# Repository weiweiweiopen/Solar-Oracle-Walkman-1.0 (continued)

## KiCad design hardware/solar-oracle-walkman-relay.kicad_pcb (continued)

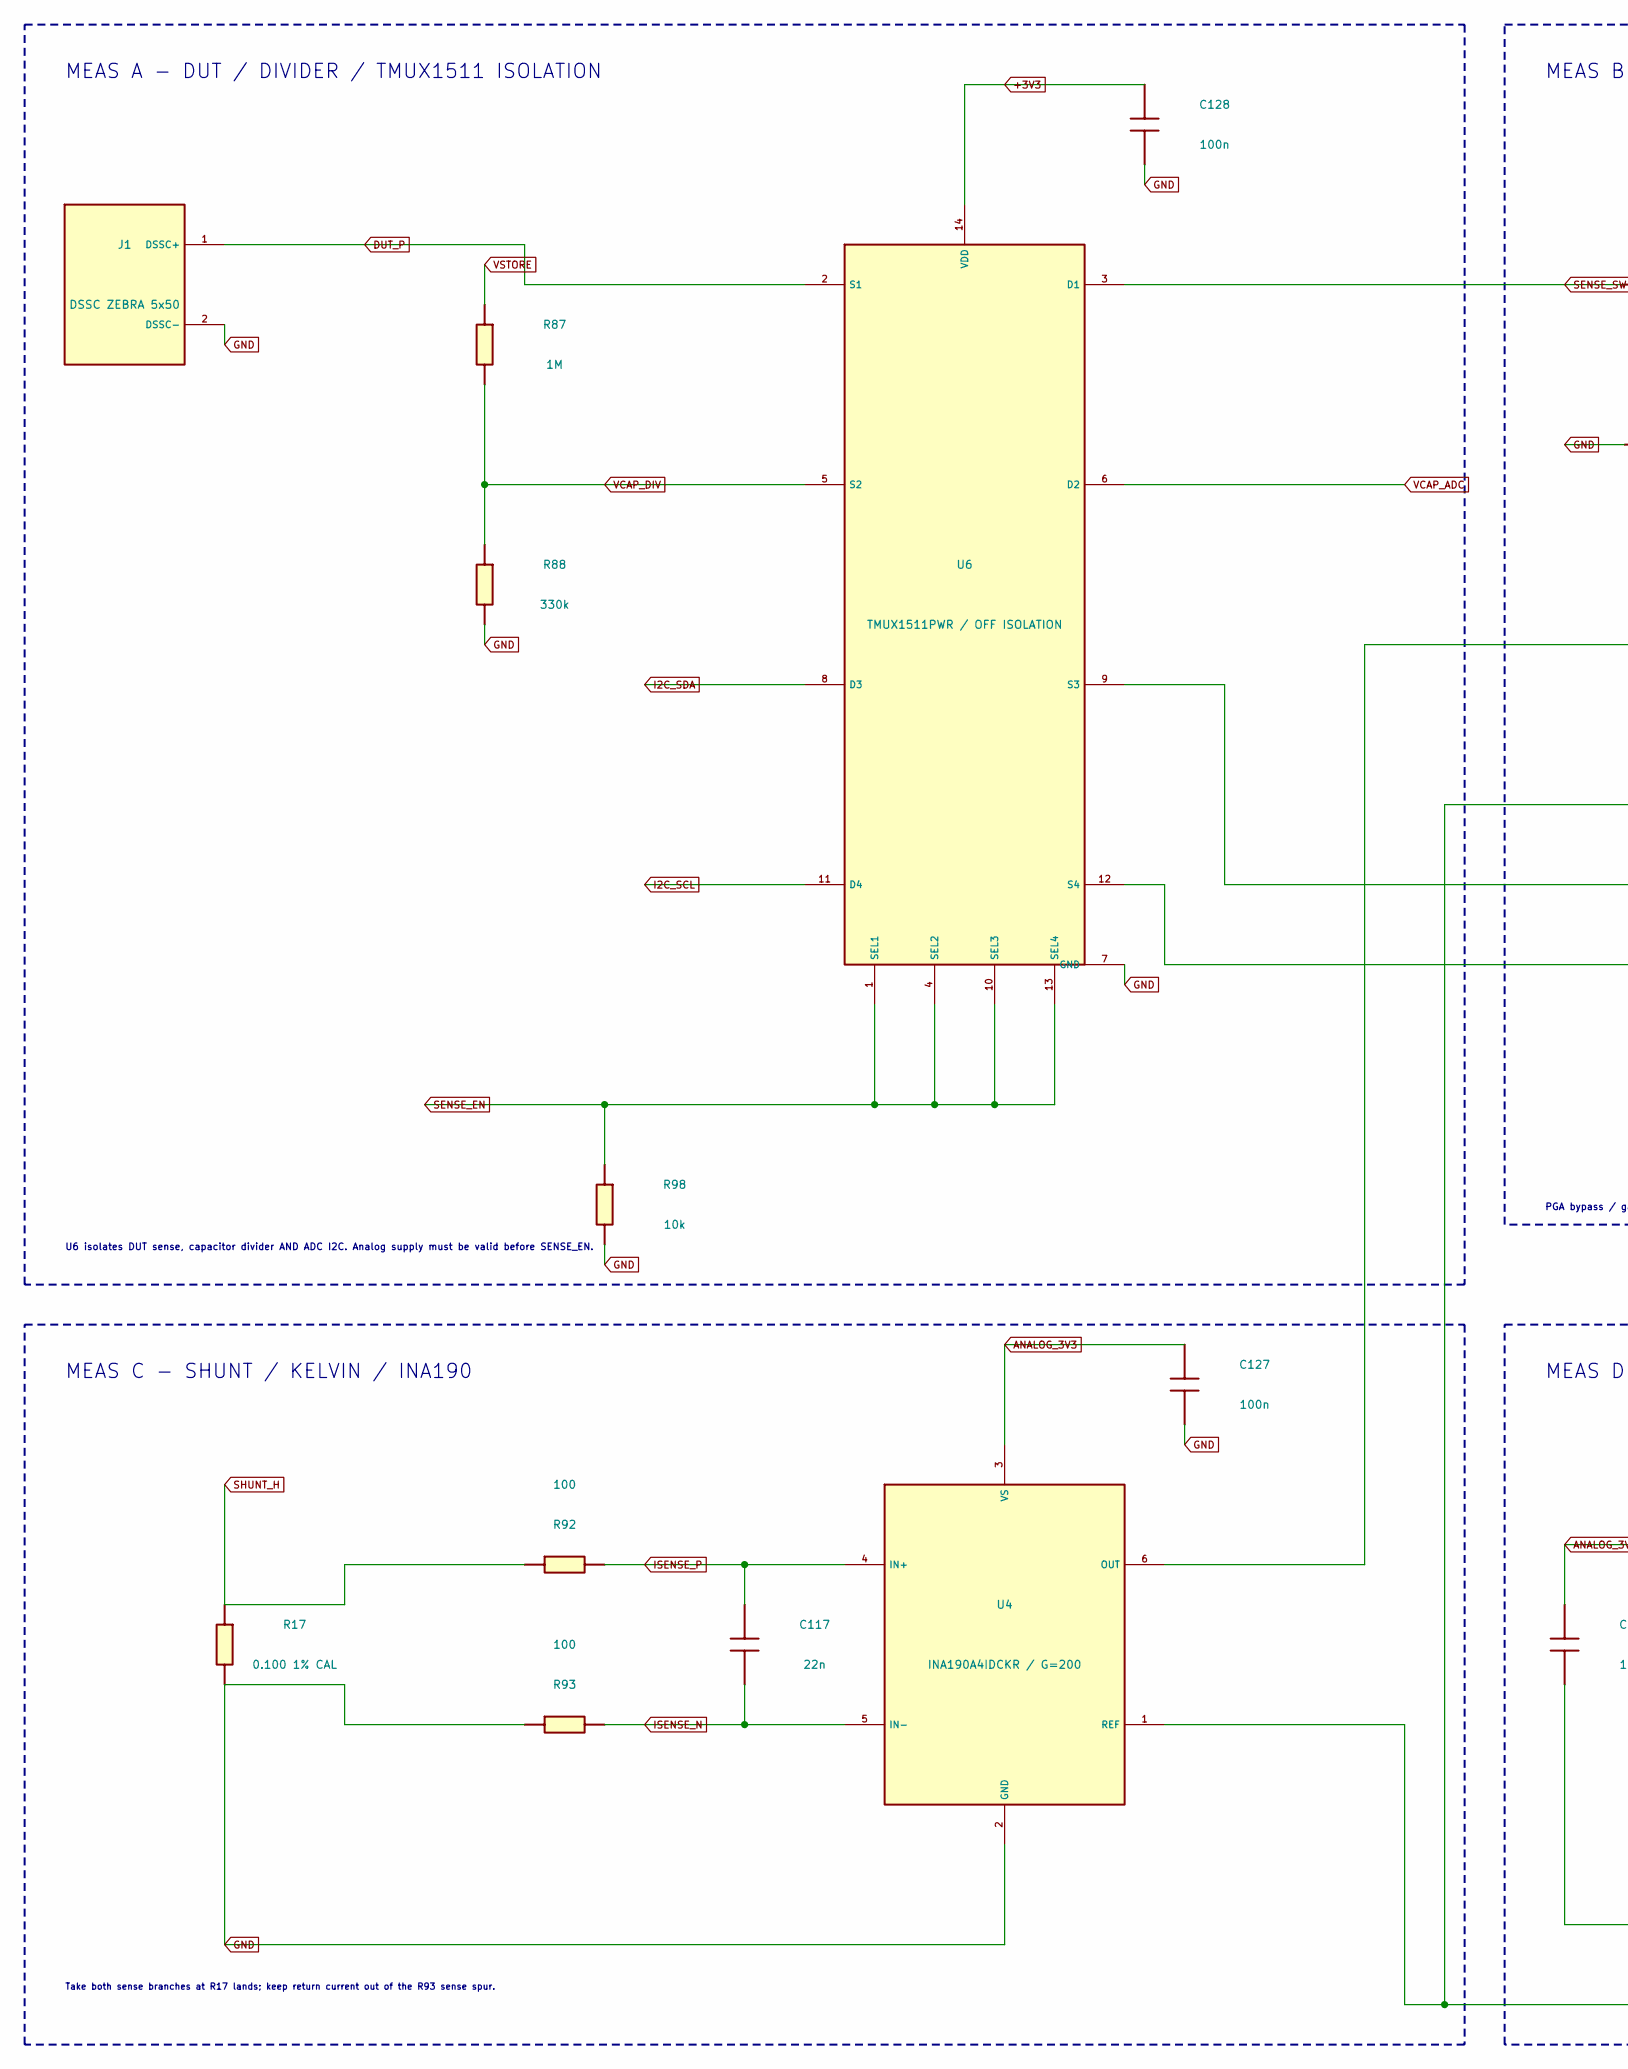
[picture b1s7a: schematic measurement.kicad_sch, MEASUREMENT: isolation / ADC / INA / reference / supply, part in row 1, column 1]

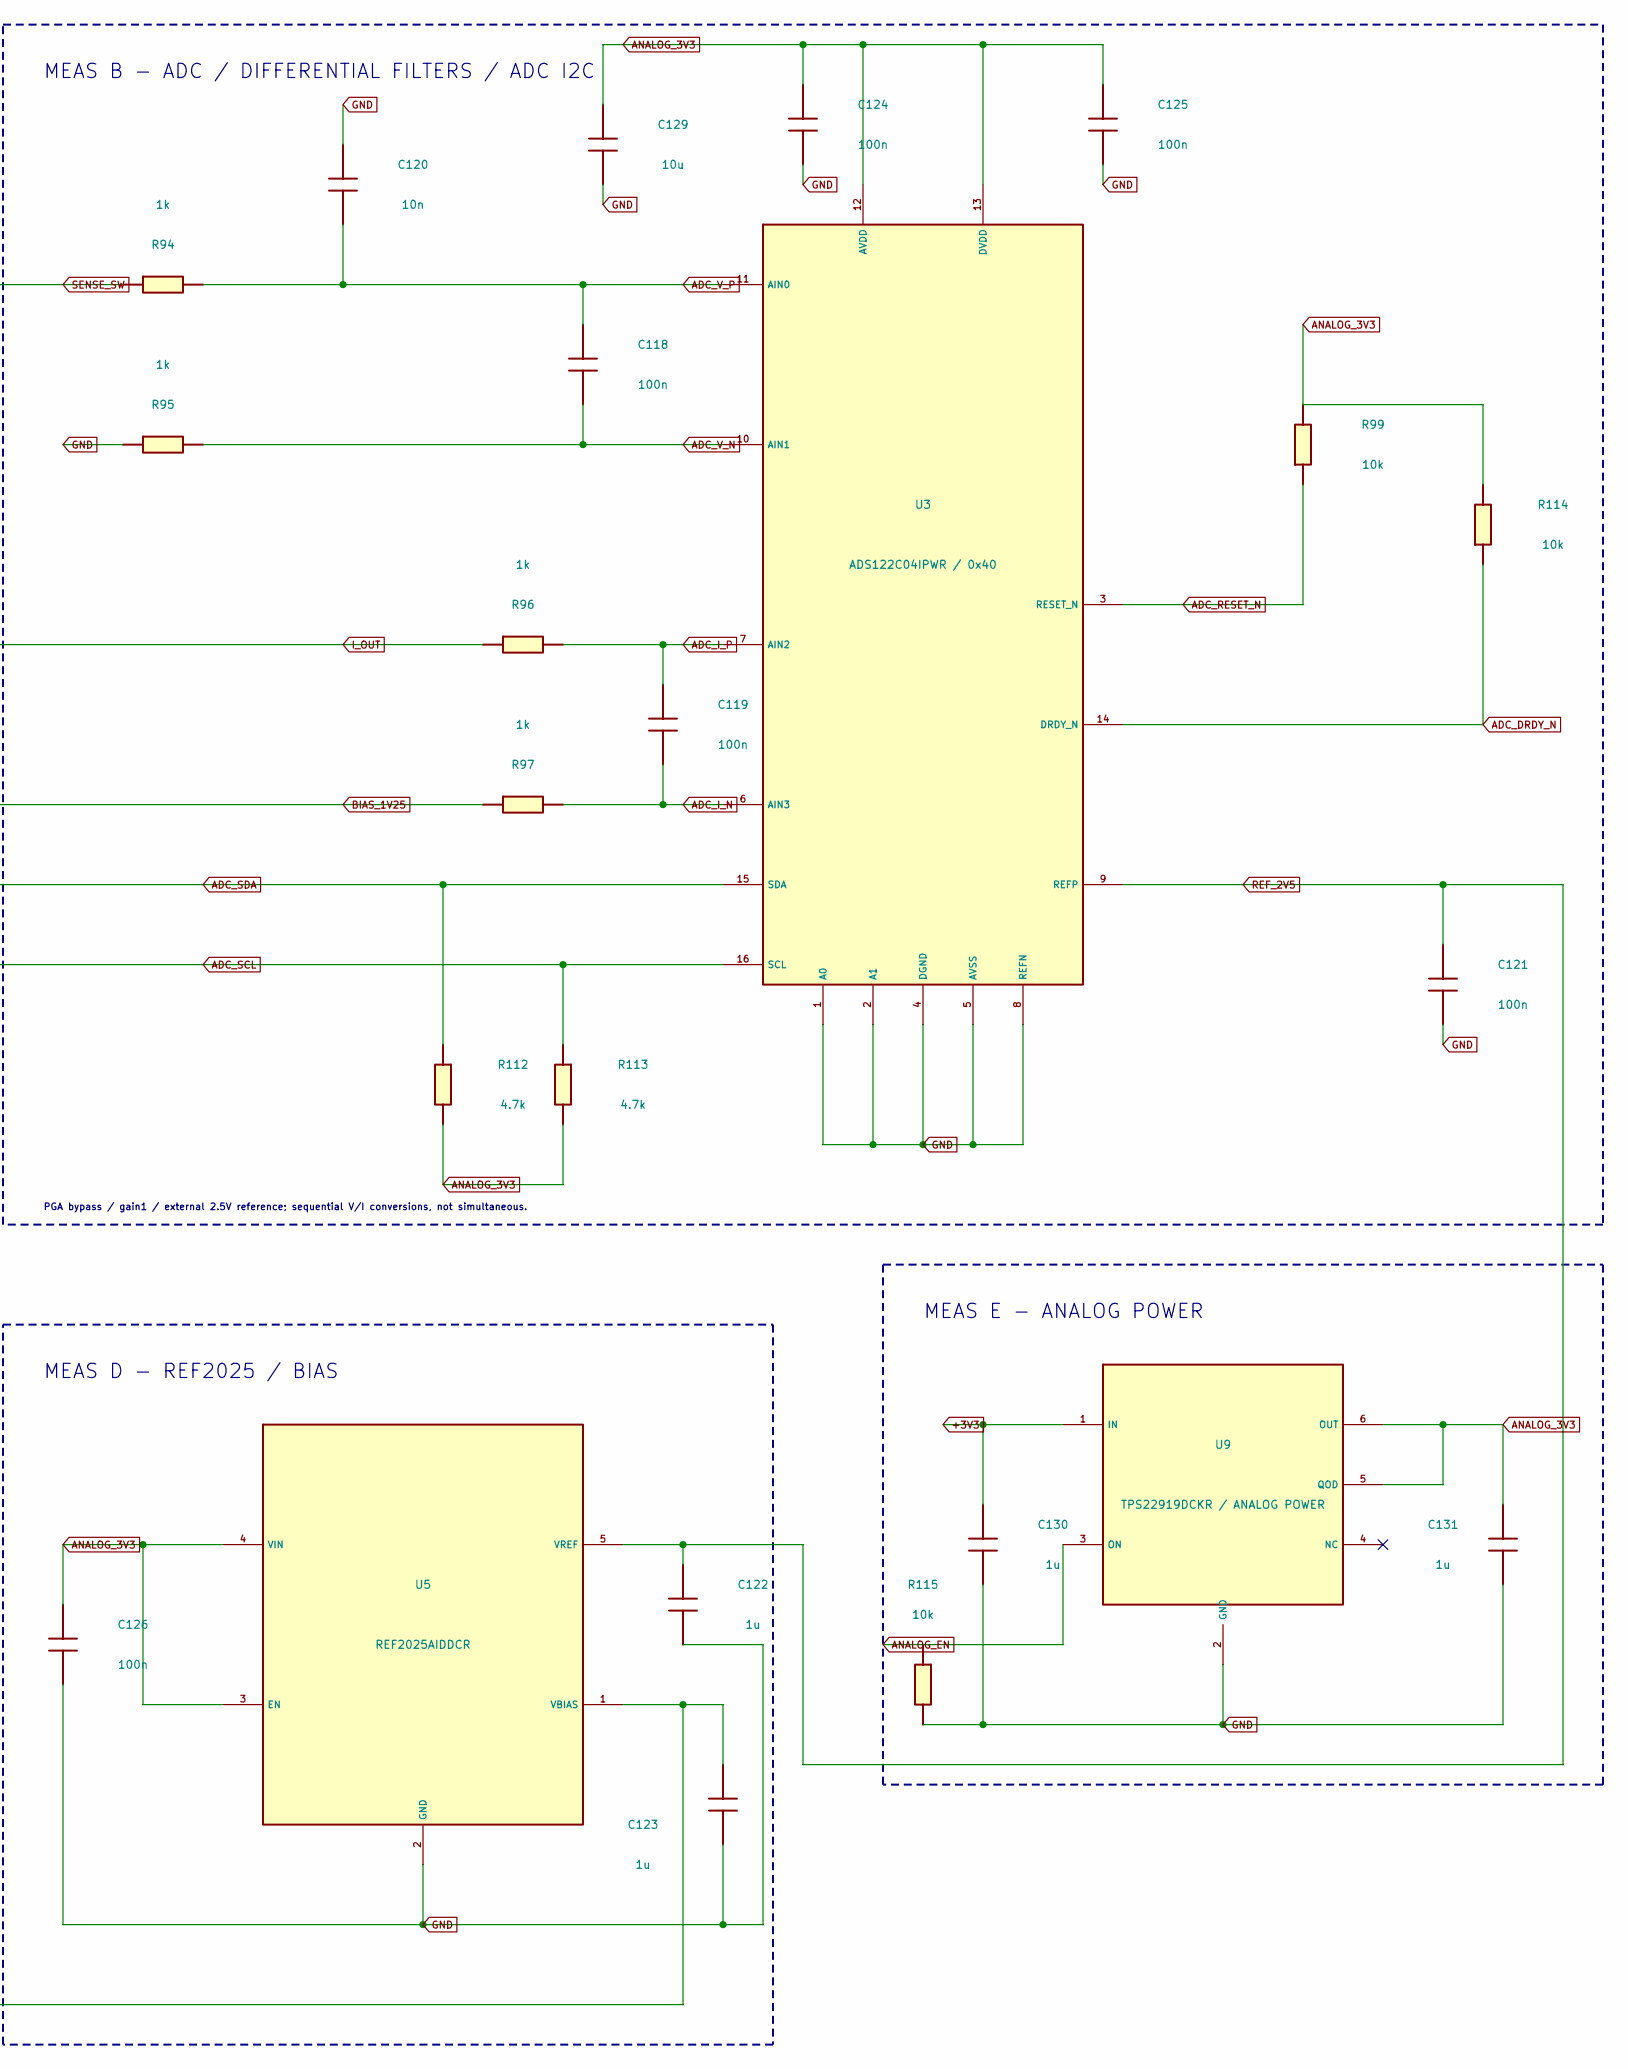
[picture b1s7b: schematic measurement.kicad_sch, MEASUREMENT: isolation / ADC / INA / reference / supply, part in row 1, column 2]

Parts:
C117: 22n; C_0805_2012Metric; MPN GRM21BR71H223KA01L
C118, C119, C121, C124, C125, C126, C127, C128: 100n; C_0805_2012Metric; MPN GRM21BR71H104KA01L
C120: 10n; C_0805_2012Metric; MPN GRM21BR71H103KA01L
C122, C123, C130, C131: 1u; C_0805_2012Metric; MPN GRM21BR71C105KA01L
C129: 10u; C_0805_2012Metric; MPN GRM21BR61C106KE15L
J1: DSSC ZEBRA 5x50; DSSC_Zebra_5x50; MPN PCB_ENIG_CONTACT
R17: 0.100 1% CAL; WSL1206; MPN WSL1206R1000FEA
R87: 1M; R_0603_1608Metric; MPN RC0603FR-071ML
R88: 330k; R_0603_1608Metric; MPN RC0603FR-07330KL
R92, R93: 100; R_0603_1608Metric; MPN RC0603FR-07100RL
R94, R95, R96, R97: 1k; R_0603_1608Metric; MPN RC0603FR-071KL
R98, R99, R114, R115: 10k; R_0603_1608Metric; MPN RC0603FR-0710KL
R112, R113: 4.7k; R_0603_1608Metric; MPN RC0603FR-074K7L
U3: ADS122C04IPWR / 0x40; TSSOP-16_4.4x5mm_P0.65mm; MPN ADS122C04IPWR
U4: INA190A4IDCKR / G=200; SOT-363_SC-70-6; MPN INA190A4IDCKR
U5: REF2025AIDDCR; SOT-23-5; MPN REF2025AIDDCR
U6: TMUX1511PWR / OFF ISOLATION; TSSOP-14_4.4x5mm_P0.65mm; MPN TMUX1511PWR
U9: TPS22919DCKR / ANALOG POWER; SOT-363_SC-70-6; MPN TPS22919DCKR

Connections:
+3V3: C128.1, C130.1, U6.14 (VDD), U9.1 (IN); also elsewhere on the board
ADC_DRDY_N: R114.1, U3.14 (DRDY_N); also elsewhere on the board
ADC_I_N: C119.2, R97.2, U3.6 (AIN3)
ADC_I_P: C119.1, R96.2, U3.7 (AIN2)
ADC_RESET_N: R99.1, U3.3 (RESET_N)
ADC_SCL: R113.1, U3.16 (SCL), U6.12 (S4)
ADC_SDA: R112.1, U3.15 (SDA), U6.9 (S3)
ADC_V_N: C118.2, R95.2, U3.10 (AIN1)
ADC_V_P: C118.1, C120.1, R94.2, U3.11 (AIN0)
ANALOG_3V3: C124.1, C125.1, C126.1, C127.1, C129.1, C131.1, R99.2, R112.2, R113.2, R114.2, U3.12 (AVDD), U3.13 (DVDD), U4.3 (VS), U5.3 (EN), U5.4 (VIN), U9.5 (QOD), U9.6 (OUT)
ANALOG_EN: R115.1, U9.3 (ON); also elsewhere on the board
BIAS_1V25: C123.1, R97.1, U4.1 (REF), U5.1 (VBIAS)
DUT_P: J1.1 (DSSC+), U6.2 (S1); also elsewhere on the board
GND: C120.2, C121.2, C122.2, C123.2, C124.2, C125.2, C126.2, C127.2, C128.2, C129.2, C130.2, C131.2, J1.2 (DSSC-), R17.2, R88.2, R93.1, R95.1, R98.2, R115.2, U3.1 (A0), U3.2 (A1), U3.4 (DGND), U3.5 (AVSS), U3.8 (REFN), U4.2 (GND), U5.2 (GND), U6.7 (GND), U9.2 (GND); also elsewhere on the board
I2C_SCL: U6.11 (D4); also elsewhere on the board
I2C_SDA: U6.8 (D3); also elsewhere on the board
ISENSE_N: C117.2, R93.2, U4.5 (IN-)
ISENSE_P: C117.1, R92.2, U4.4 (IN+)
I_OUT: R96.1, U4.6 (OUT)
REF_2V5: C121.1, C122.1, U3.9 (REFP), U5.5 (VREF)
SENSE_EN: R98.1, U6.1 (SEL1), U6.4 (SEL2), U6.10 (SEL3), U6.13 (SEL4); also elsewhere on the board
SENSE_SW: R94.1, U6.3 (D1)
SHUNT_H: R17.1, R92.1; also elsewhere on the board
VCAP_ADC: U6.6 (D2); also elsewhere on the board
VCAP_DIV: R87.2, R88.1, U6.5 (S2)
VSTORE: R87.1; also elsewhere on the board

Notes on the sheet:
MEAS D - REF2025 / BIAS
MEAS B - ADC / DIFFERENTIAL FILTERS / ADC I2C
PGA bypass / gain1 / external 2.5V reference; sequential V/I conversions, not simultaneous.
MEAS A - DUT / DIVIDER / TMUX1511 ISOLATION
MEAS C - SHUNT / KELVIN / INA190
MEAS E - ANALOG POWER
U6 isolates DUT sense, capacitor divider AND ADC I2C. Analog supply must be valid before SENSE_EN.
Take both sense branches at R17 lands; keep return current out of the R93 sense spur.

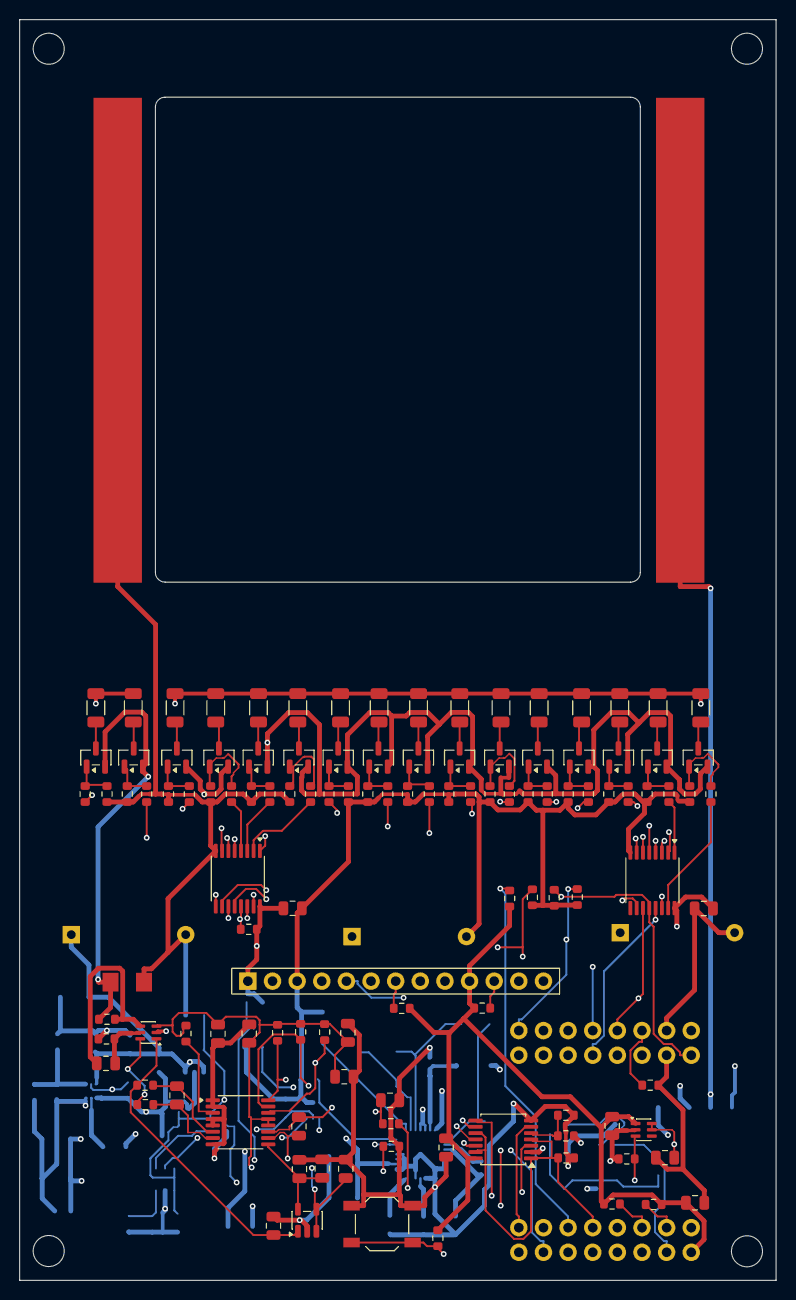
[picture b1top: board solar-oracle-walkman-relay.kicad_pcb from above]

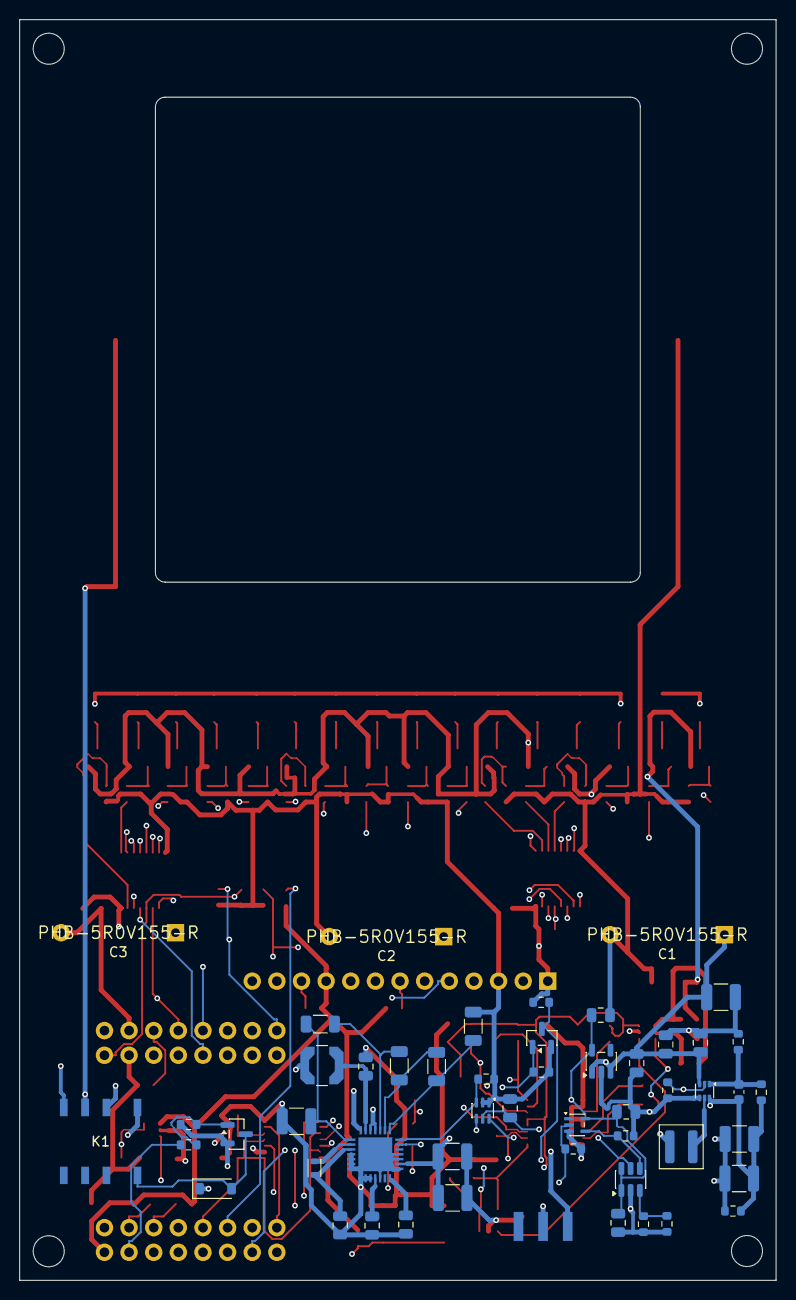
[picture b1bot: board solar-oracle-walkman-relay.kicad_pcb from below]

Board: 4 copper layers, 78.0 x 130.0 mm, 175 parts (52 on the bottom side), 118 nets.

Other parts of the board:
MH1, MH2, MH3, MH4: M3 D3.2 / HEAD5.5 / NO WASHER; Case_M3_D3.2_Head5.5

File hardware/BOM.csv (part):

ref,quantity,value,MPN,footprint,sheet,connected_power_domains,note
J2,1,LOLIN S3 MINI V1.0.0 / SOCKET,LOLIN S3 MINI V1.0.0,solar_oracle:LOLIN_S3_Mini_V1,control,+3V3;GND;MODULE_VBUS,
J3,1,ADAFRUIT 6366 / 1x13 FEMALE,SSW-113-01-T-S,solar_oracle:EPD_6366_Socket13,control,+3V3;GND,"13-pin SPI socket; 8.51mm nominal body; display rotated180, VIN left/ENA right; pin2 regulator output NC; GPIO35 SRAM CS; map GPIO20260920"
U1,1,SN74HC595PWR,SN74HC595PWR,Package_SO:TSSOP-16_4.4x5mm_P0.65mm,control,+3V3;GND,
C101,1,100n,GRM21BR71H104KA01L,Capacitor_SMD:C_0805_2012Metric,control,+3V3;GND,
U2,1,SN74HC595PWR,SN74HC595PWR,Package_SO:TSSOP-16_4.4x5mm_P0.65mm,control,+3V3;GND,
C102,1,100n,GRM21BR71H104KA01L,Capacitor_SMD:C_0805_2012Metric,control,+3V3;GND,
R101,1,10k,RC0603FR-0710KL,Resistor_SMD:R_0603_1608Metric,control,+3V3,
R102,1,10k,RC0603FR-0710KL,Resistor_SMD:R_0603_1608Metric,control,+3V3,
R103,1,10k,RC0603FR-0710KL,Resistor_SMD:R_0603_1608Metric,control,GND,
R104,1,10k,RC0603FR-0710KL,Resistor_SMD:R_0603_1608Metric,control,GND,
R105,1,10k,RC0603FR-0710KL,Resistor_SMD:R_0603_1608Metric,control,GND,
R106,1,10k,RC0603FR-0710KL,Resistor_SMD:R_0603_1608Metric,control,GND,
R107,1,10k,RC0603FR-0710KL,Resistor_SMD:R_0603_1608Metric,control,+3V3,
R108,1,10k,RC0603FR-0710KL,Resistor_SMD:R_0603_1608Metric,control,+3V3,
R109,1,10k,RC0603FR-0710KL,Resistor_SMD:R_0603_1608Metric,control,+3V3,
C103,1,10u,GRM21BR61C106KE15L,Capacitor_SMD:C_0805_2012Metric,control,+3V3;GND,
SW1,1,MEASURE,TL3342F160QG,Button_Switch_SMD:SW_SPST_TL3342,control,GND,
U7,1,AEM10941 / CFG=000,10AEM10941C0001,solar_oracle:AEM10941_QFN28_EP3.5,power,GND;HARV_P;VSTORE,
L1,1,22uH,LPS4018-223MRC,Inductor_SMD:L_Coilcraft_LPS4018,power,,
L2,1,10uH,MLZ1608N100LT000,Inductor_SMD:L_TDK_MLZ1608,power,,
C104,1,22u,GRM32ER61A226KE20L,Capacitor_SMD:C_1210_3225Metric,power,GND,
C105,1,10u,GRM21BR61C106KE15L,Capacitor_SMD:C_0805_2012Metric,power,GND,
C106,1,10u,GRM21BR61C106KE15L,Capacitor_SMD:C_0805_2012Metric,power,GND,
C107,1,10u,GRM21BR61C106KE15L,Capacitor_SMD:C_0805_2012Metric,power,GND,
C108,1,10u,GRM21BR61C106KE15L,Capacitor_SMD:C_0805_2012Metric,power,GND,
C109,1,100u,GRM32ER60J107ME20L,Capacitor_SMD:C_1210_3225Metric,power,GND;VSTORE,Verify effective DC-bias capacitance
C110,1,100u,GRM32ER60J107ME20L,Capacitor_SMD:C_1210_3225Metric,power,GND;VSTORE,Verify effective DC-bias capacitance
C111,1,22u,GRM32ER61A226KE20L,Capacitor_SMD:C_1210_3225Metric,power,GND;VSTORE,
R80,1,549k,TNPW1206549KBEEA,Resistor_SMD:R_1206_3216Metric,power,GND,0.1% threshold resistor; exact sourcing to qualify
R81,1,9.31k,TNPW12069K31BEEA,Resistor_SMD:R_1206_3216Metric,power,,0.1% threshold resistor; exact sourcing to qualify
R82,1,143k,TNPW1206143KBEEA,Resistor_SMD:R_1206_3216Metric,power,,0.1% threshold resistor; exact sourcing to qualify
R83,1,1.74M,TNPW12061M74BEEA,Resistor_SMD:R_1206_3216Metric,power,,0.1% threshold resistor; exact sourcing to qualify
C1,1,1.5F 5V PHB,PHB-5R0V155-R,solar_oracle:PHB_5R0V155_R_LaidDown_Provisional,power,GND;VSTORE,PARALLEL 5V pack; + pad1 longer lead; max17.3x9x22mm/P11.8; equalize before assembly; no reflow
C2,1,1.5F 5V PHB,PHB-5R0V155-R,solar_oracle:PHB_5R0V155_R_LaidDown_Provisional,power,GND;VSTORE,PARALLEL 5V pack; + pad1 longer lead; max17.3x9x22mm/P11.8; equalize before assembly; no reflow
C3,1,1.5F 5V PHB,PHB-5R0V155-R,solar_oracle:PHB_5R0V155_R_LaidDown_Provisional,power,GND;VSTORE,PARALLEL 5V pack; + pad1 longer lead; max17.3x9x22mm/P11.8; equalize before assembly; no reflow
U8,1,TPS61023DRLR / 5V,TPS61023DRLR,Package_TO_SOT_SMD:SOT-563,power,GND;SOLAR_5V;VSTORE,
L3,1,1uH,XEL4030-102MEC,solar_oracle:Coilcraft_XEL4030,power,VSTORE,
R84,1,732k,RC0603FR-07732KL,Resistor_SMD:R_0603_1608Metric,power,SOLAR_5V,
R85,1,100k,RC0603FR-07100KL,Resistor_SMD:R_0603_1608Metric,power,GND,
R86,1,47k,RC0603FR-0747KL,Resistor_SMD:R_0603_1608Metric,always_on,GND,Fail-low bias; approx95uA when READY high; qualify loaded STATUS0 voltage
C112,1,220p,GRM1885C1H221JA01D,Capacitor_SMD:C_0603_1608Metric,power,SOLAR_5V,
C113,1,10u,GRM21BR61C106KE15L,Capacitor_SMD:C_0805_2012Metric,power,GND;VSTORE,
C114,1,100n,GRM21BR71H104KA01L,Capacitor_SMD:C_0805_2012Metric,power,GND;VSTORE,
C115,1,22u,GRM32ER61A226KE20L,Capacitor_SMD:C_1210_3225Metric,power,GND;SOLAR_5V,
C116,1,22u,GRM32ER61A226KE20L,Capacitor_SMD:C_1210_3225Metric,power,GND;SOLAR_5V,
JP1,1,SLIDE / OFF BEFORE USB,EGJ1210AAG2R,solar_oracle:EGJ1210AAG2R_Side,power,MODULE_VBUS;SOLAR_5V,"Side-actuated SPDT used ON/OFF; 1=SOLAR_5V common, 2=MODULE_VBUS, 3=NC; 0.5A at 12VDC; OFF before USB"
R87,1,1M,RC0603FR-071ML,Resistor_SMD:R_0603_1608Metric,measurement,VSTORE,
R88,1,330k,RC0603FR-07330KL,Resistor_SMD:R_0603_1608Metric,measurement,GND,
Q18,1,AO3400A / WARN LEVEL,AO3400A,Package_TO_SOT_SMD:SOT-23,power,GND,
R110,1,100k,RC0603FR-07100KL,Resistor_SMD:R_0603_1608Metric,power,+3V3,
R111,1,1M,RC0603FR-071ML,Resistor_SMD:R_0603_1608Metric,power,GND,
J1,1,DSSC ZEBRA 5x50,PCB_ENIG_CONTACT,solar_oracle:DSSC_Zebra_5x50,measurement,DUT_P;GND,66x66 glass; clamp and electrode registration require physical qualification
Q17,1,AO3400A / RELAY COIL,AO3400A,Package_TO_SOT_SMD:SOT-23,switching,GND,Low-side coil driver; high SCAN_MODE energizes relay
R90,1,1k,RC0603FR-071KL,Resistor_SMD:R_0603_1608Metric,switching,,
R91,1,47k,RC0603FR-0747KL,Resistor_SMD:R_0603_1608Metric,switching,GND,
D1,1,1N4148W / FLYBACK,1N4148W-7-F,Diode_SMD:D_SOD-123,switching,MODULE_VBUS,"Flyback diode: K=pad1 to+5V, A=pad2 to coil low"
U3,1,ADS122C04IPWR / 0x40,ADS122C04IPWR,Package_SO:TSSOP-16_4.4x5mm_P0.65mm,measurement,ANALOG_3V3;GND,
U4,1,INA190A4IDCKR / G=200,INA190A4IDCKR,Package_TO_SOT_SMD:SOT-363_SC-70-6,measurement,ANALOG_3V3;GND,
U5,1,REF2025AIDDCR,REF2025AIDDCR,Package_TO_SOT_SMD:SOT-23-5,measurement,ANALOG_3V3;GND,
U6,1,TMUX1511PWR / OFF ISOLATION,TMUX1511PWR,Package_SO:TSSOP-14_4.4x5mm_P0.65mm,measurement,+3V3;DUT_P;GND,
R17,1,0.100 1% CAL,WSL1206R1000FEA,solar_oracle:WSL1206,measurement,GND;SHUNT_H,1206 0.1ohm 1% 0.25W at 70C +/-75ppm/C shunt; separate PCB Kelvin traces and assembled gain calibration required
R92,1,100,RC0603FR-07100RL,Resistor_SMD:R_0603_1608Metric,measurement,SHUNT_H,
R93,1,100,RC0603FR-07100RL,Resistor_SMD:R_0603_1608Metric,measurement,GND,
R94,1,1k,RC0603FR-071KL,Resistor_SMD:R_0603_1608Metric,measurement,,
R95,1,1k,RC0603FR-071KL,Resistor_SMD:R_0603_1608Metric,measurement,GND,
R96,1,1k,RC0603FR-071KL,Resistor_SMD:R_0603_1608Metric,measurement,,
R97,1,1k,RC0603FR-071KL,Resistor_SMD:R_0603_1608Metric,measurement,,
R98,1,10k,RC0603FR-0710KL,Resistor_SMD:R_0603_1608Metric,measurement,GND,
R99,1,10k,RC0603FR-0710KL,Resistor_SMD:R_0603_1608Metric,measurement,ANALOG_3V3,
R112,1,4.7k,RC0603FR-074K7L,Resistor_SMD:R_0603_1608Metric,measurement,ANALOG_3V3,
R113,1,4.7k,RC0603FR-074K7L,Resistor_SMD:R_0603_1608Metric,measurement,ANALOG_3V3,
R114,1,10k,RC0603FR-0710KL,Resistor_SMD:R_0603_1608Metric,measurement,ANALOG_3V3,
C117,1,22n,GRM21BR71H223KA01L,Capacitor_SMD:C_0805_2012Metric,measurement,,
C118,1,100n,GRM21BR71H104KA01L,Capacitor_SMD:C_0805_2012Metric,measurement,,
C119,1,100n,GRM21BR71H104KA01L,Capacitor_SMD:C_0805_2012Metric,measurement,,
C120,1,10n,GRM21BR71H103KA01L,Capacitor_SMD:C_0805_2012Metric,measurement,GND,
C121,1,100n,GRM21BR71H104KA01L,Capacitor_SMD:C_0805_2012Metric,measurement,GND,
C122,1,1u,GRM21BR71C105KA01L,Capacitor_SMD:C_0805_2012Metric,measurement,GND,
C123,1,1u,GRM21BR71C105KA01L,Capacitor_SMD:C_0805_2012Metric,measurement,GND,
C124,1,100n,GRM21BR71H104KA01L,Capacitor_SMD:C_0805_2012Metric,measurement,ANALOG_3V3;GND,
C125,1,100n,GRM21BR71H104KA01L,Capacitor_SMD:C_0805_2012Metric,measurement,ANALOG_3V3;GND,
C126,1,100n,GRM21BR71H104KA01L,Capacitor_SMD:C_0805_2012Metric,measurement,ANALOG_3V3;GND,
C127,1,100n,GRM21BR71H104KA01L,Capacitor_SMD:C_0805_2012Metric,measurement,ANALOG_3V3;GND,
C128,1,100n,GRM21BR71H104KA01L,Capacitor_SMD:C_0805_2012Metric,measurement,+3V3;GND,
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
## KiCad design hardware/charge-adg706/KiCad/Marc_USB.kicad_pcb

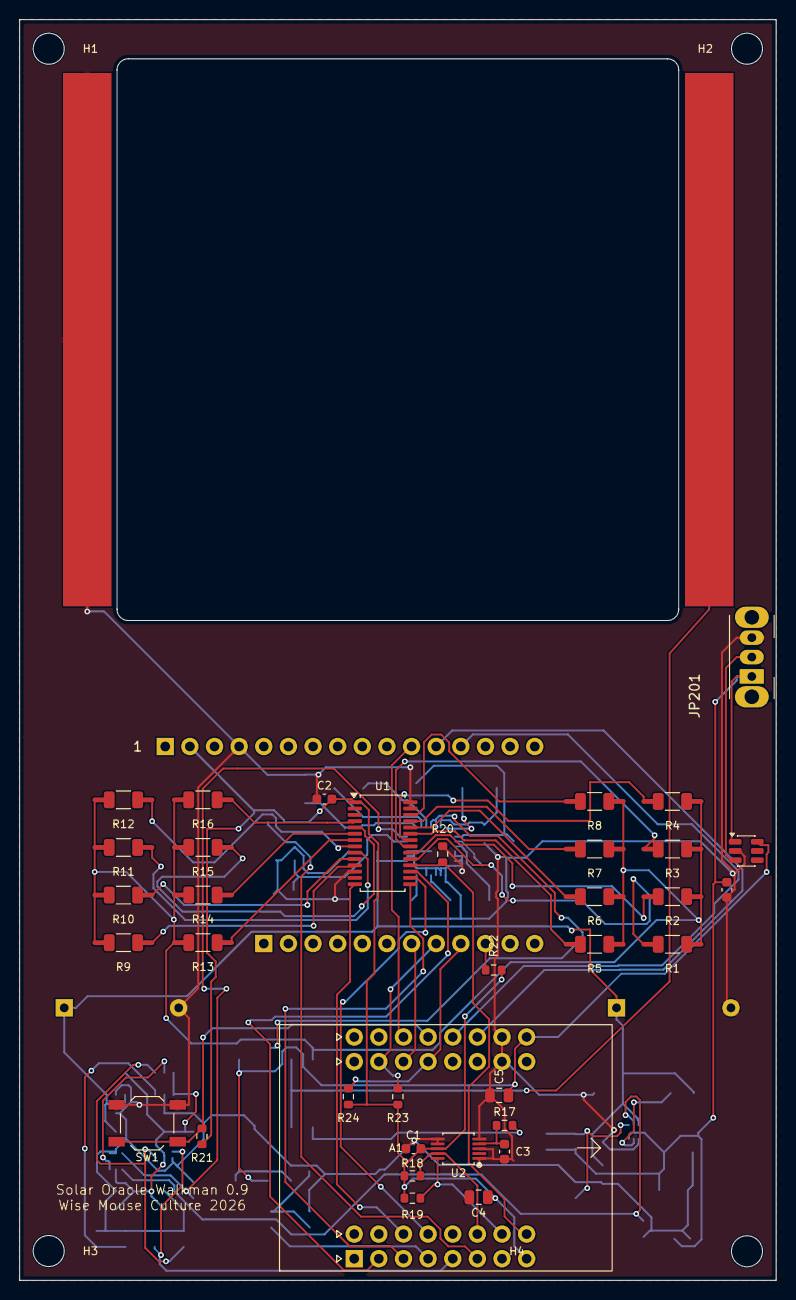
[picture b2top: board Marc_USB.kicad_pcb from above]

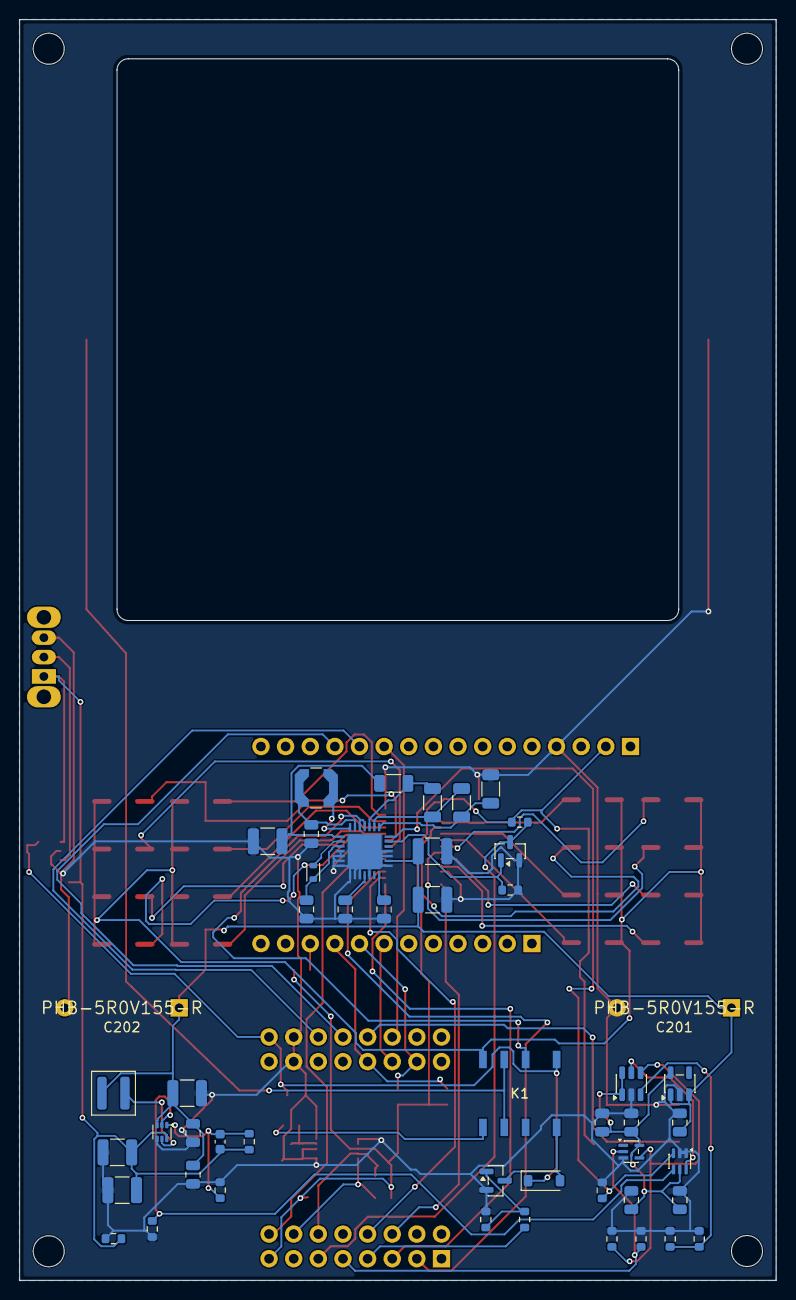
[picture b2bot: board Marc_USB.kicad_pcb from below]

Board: 2 copper layers, 78.0 x 130.0 mm, 92 parts (50 on the bottom side), 66 nets.

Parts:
A1: LOLIN S3 Mini V1.0.0; LOLIN_S3_MINI_V1
C1, C2: 100n; C_0603_1608Metric
C3: 10n; C_0603_1608Metric
C4, C5: 10u 10V X7R; C_0805_2012Metric
C201, C202: 1.5F 5V PHB; PHB_5R0V155_R_LaidDown_Provisional
C304, C311, C315, C316: 22u; C_1210_3225Metric
C305, C306, C307, C308, C313: 10u; C_0805_2012Metric
C309, C310: 100u; C_1210_3225Metric
C312: 220p; C_0603_1608Metric
C314, C334, C335, C336: 100n; C_0805_2012Metric
C317: 1uF 10V X7R; C_0603_1608Metric
C332, C333: 1u; C_0805_2012Metric
D201: 1N4148W / FLYBACK; D_SOD-123
H1, H2, H3, H4: NPTH 3.2mm; MountingHole_3.2mm_M3
J1: DSSC single-cell collector; DSSC_Collector_58mm
J3: Adafruit 4814 SSD1680 250x122; Adafruit_4814_FeatherWing_Mating
JP201: C&K OS102011MA1QN1; SW_Slide_SPDT_Angled_CK_OS102011MA1Q
K1: G6K-2F-Y DC5; G6K_2F_Y
L201: 22uH; L_Coilcraft_LPS4018
L202: 10uH; L_TDK_MLZ1608
L203: 1uH; Coilcraft_XEL4030
Q217: AO3400A / RELAY COIL; SOT-23
Q218: AO3400A / WARN LEVEL; SOT-23
R1: 1M CANDIDATE; R_1206_3216Metric
R2: 20k CANDIDATE; R_1206_3216Metric
R3: 8.2k CANDIDATE; R_1206_3216Metric
R4: 4.3k CANDIDATE; R_1206_3216Metric
R5: 2.2k CANDIDATE; R_1206_3216Metric
R6: 1k CANDIDATE; R_1206_3216Metric
R7: 750 CANDIDATE; R_1206_3216Metric
R8: 470 CANDIDATE; R_1206_3216Metric
R9: 330 CANDIDATE; R_1206_3216Metric
R10: 220 CANDIDATE; R_1206_3216Metric
R11: 150 CANDIDATE; R_1206_3216Metric
R12: 100 CANDIDATE; R_1206_3216Metric
R13: 75 CANDIDATE; R_1206_3216Metric
R14: 68 CANDIDATE; R_1206_3216Metric
R15: 62 CANDIDATE; R_1206_3216Metric
R16: 56 CANDIDATE; R_1206_3216Metric
R17, R290: 1k; R_0603_1608Metric
R18, R19: 4.7k; R_0603_1608Metric
R20, R21, R22, R23, R24, R320, R321, R322: 10k; R_0603_1608Metric
R280: 549k; R_1206_3216Metric
R281: 9.31k; R_1206_3216Metric
R282: 143k; R_1206_3216Metric
R283: 1.74M; R_1206_3216Metric
R284: 732k; R_0603_1608Metric
R285, R310, R323: 100k; R_0603_1608Metric
R286, R291: 47k; R_0603_1608Metric
R311: 1M; R_0603_1608Metric
R318: 107k; R_0603_1608Metric
R319: 124k; R_0603_1608Metric
SW1: MEASURE / SCALE; SW_SPST_TL3342
U1: ADG706BRUZ-REEL7; TSSOP-28_4.4x9.7mm_P0.65mm
U2: ADS1115IDGSR / 0x48; TSSOP-10_3x3mm_P0.5mm
U207: AEM10941 / CFG=000; AEM10941_QFN28_EP3.5
U208: TPS61023DRLR / 5V; SOT-563
U210: TPS7A0233PDBVR / AON ONLY; SOT-23-5
U211: TPL5111DDCR / 600s; SOT-23-6
U212: SN74LVC1G97DCKR / SCHMITT AND; SOT-363_SC-70-6
U213: SN74LVC1G17DCKR / DONE ISOLATION; SOT-353_SC-70-5
U214: TPS22917DBV; SOT-23-6

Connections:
ADC_IN: C3.1, R17.2, U2.4
AON_3V3: C333.1, C334.1, C335.1, C336.1, U210.5, U211.1, U211.6, U212.5, U213.5
BOOST_EN: R322.1, U208.2, U212.4
BUTTON_N: A1.J3.4, R21.2, SW1.1
DUT_P: J1.1, K1.3, K1.6
EPD_CS: A1.J4.2, J3.21, R23.2
EPD_DC: A1.J4.3, J3.22
GND: A1.J3.7, A1.J4.7, C1.2, C2.2, C3.2, C4.2, C5.2, C201.2, C202.2, C304.2, C305.2, C306.2, C307.2, C308.2, C309.2, C310.2, C311.2, C313.2, C314.2, C315.2, C316.2, C317.2, C332.2, C333.2, C334.2, C335.2, C336.2, J1.2, J3.4, JP201.3, Q217.2, Q218.2, R20.2, R280.2, R285.2, R286.2, R291.2, R311.2, R318.2, R319.2, R320.2, R321.2, R322.2, R323.2, SW1.2, U1.12, U1.27, U1.28, U2.1, U2.3, U2.5, U2.6, U2.7, U207.4, U207.5, U207.6, U207.7, U207.8, U207.9, U207.10, U207.12, U207.15, U207.17, U207.18, U207.29, U208.4, U210.2, U211.2, U212.1, U212.2, U213.3, U214.2
HARV_P: K1.2, U207.25, U207.26
I2C_SCL: A1.J5.7, R19.2, U2.10
I2C_SDA: A1.J5.6, R18.2, U2.9
LOAD_00: R1.2, U1.19
LOAD_01: R2.2, U1.20
LOAD_02: R3.2, U1.21
LOAD_03: R4.2, U1.22
LOAD_04: R5.2, U1.23
LOAD_05: R6.2, U1.24
LOAD_06: R7.2, U1.25
LOAD_07: R8.2, U1.26
LOAD_08: R9.2, U1.11
LOAD_09: R10.2, U1.10
LOAD_10: R11.2, U1.9
LOAD_11: R12.2, U1.8
LOAD_12: R13.2, U1.7
LOAD_13: R14.2, U1.6
LOAD_14: R15.2, U1.5
LOAD_15: R16.2, U1.4
LOAD_P: K1.4, R1.1, R2.1, R3.1, R4.1, R5.1, R6.1, R7.1, R8.1, R9.1, R10.1, R11.1, R12.1, R13.1, R14.1, R15.1, R16.1
MCU_3V3: A1.J2.8, C1.1, C2.1, C4.1, J3.2, R18.1, R19.1, R21.1, R22.1, R23.1, R24.1, R310.2, U1.1, U2.8
MCU_DONE: A1.J2.5, R320.1, U213.2
MODULE_VBUS: A1.J3.8, C5.1, D201.1, K1.1, U214.6
MUX_A0: A1.J2.2, U1.17
MUX_A1: A1.J5.4, U1.16
MUX_A2: A1.J2.3, U1.15
MUX_A3: A1.J5.3, U1.14
MUX_EN: A1.J5.8, R20.1, U1.18
P5_FB: C312.2, R284.2, R285.1, U208.1
P5_SW: L203.2, U208.5
PM_BOOST: C304.1, R283.1, U207.1
PM_BUCK: C306.1, L202.2, U207.3
PM_BUFSRC: C305.1, L201.1, U207.27
PM_HVOUT: C308.1, U207.14
PM_LVOUT: C307.1, U207.11
PM_READY: R286.1, U207.21, U212.3
PM_SWBOOST: L201.2, U207.28
PM_SWBUCK: L202.1, U207.2
PM_WARN: Q218.1, R311.1, U207.20
POWER_WARN_N: A1.J2.6, Q218.3, R310.1
RELAY_COIL_LOW: D201.2, K1.8, Q217.3
SCAN_GATE: Q217.1, R290.2, R291.1
SCAN_MODE: A1.J2.4, R290.1
SD_CS_N: J3.19, R22.2
SENSE_P: K1.5, R17.1
SET_CHRDY: R281.1, R282.2, U207.23
SET_OVCH: R280.1, R281.2, U207.22
SET_OVDIS: R282.1, R283.2, U207.24
SOLAR_5V: C312.1, C315.1, C316.1, C317.1, JP201.1, R284.1, R323.1, U208.6, U214.1
SOLAR_EN: JP201.2, U214.3
SPI_MISO: A1.J3.5, J3.13
SPI_MOSI: A1.J3.6, J3.12
SPI_SCK: A1.J3.3, J3.11
SRAM_CS: A1.J4.4, J3.20, R24.2
TIMER_DELAY: R318.1, R319.1, U211.3
TIMER_DONE: R321.1, U211.4, U213.4
TIMER_REQUEST: U211.5, U212.6
VSTORE: C201.1, C202.1, C309.1, C310.1, C311.1, C313.1, C314.1, C332.1, L203.1, U207.16, U208.3, U210.1, U210.3

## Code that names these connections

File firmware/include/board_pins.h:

#pragma once
#include <cstddef>
// Approved relay-board routability map GPIO20260920. GPIO numbers, NOT connector pad numbers.
// Board: LOLIN S3 MINI V1.0.0 / ESP32-S3FH4R2 (quad flash/PSRAM).
namespace solar_oracle { namespace pins {
constexpr const char* REVISION = "GPIO20260920";
constexpr int ADC_DRDY_N = 2; // carrier J2 pad 2
constexpr int ANALOG_EN = 11; // carrier J2 pad 6
constexpr int BUTTON_N = 13; // carrier J2 pad 5
constexpr int EPD_BUSY = 17; // carrier J2 pad 22
constexpr int EPD_CS_N = 33; // carrier J2 pad 17
constexpr int EPD_DC = 21; // carrier J2 pad 21
constexpr int EPD_ENA = 16; // carrier J2 pad 30
constexpr int EPD_MISO = 37; // carrier J2 pad 18
constexpr int EPD_MOSI = 38; // carrier J2 pad 19
constexpr int EPD_RST_N = 36; // carrier J2 pad 27
constexpr int EPD_SCK = 44; // carrier J2 pad 26
constexpr int EPD_SRAM_CS_N = 35; // carrier J2 pad 28
constexpr int I2C_SCL = 9; // carrier J2 pad 15
constexpr int I2C_SDA = 8; // carrier J2 pad 14
constexpr int LOAD_OE_N = 34; // carrier J2 pad 20
constexpr int MCU_DONE = 12; // carrier J2 pad 4
constexpr int POWER_WARN_N = 7; // carrier J2 pad 13
constexpr int SCAN_MODE = 10; // carrier J2 pad 7
constexpr int SENSE_EN = 6; // carrier J2 pad 12
constexpr int SR_CLEAR_N = 5; // carrier J2 pad 11
constexpr int SR_CLOCK = 18; // carrier J2 pad 29
constexpr int SR_DATA = 43; // carrier J2 pad 25
constexpr int SR_LATCH = 15; // carrier J2 pad 24
constexpr int VCAP_ADC = 1; // carrier J2 pad 9
constexpr int ASSIGNED[] = {ADC_DRDY_N, ANALOG_EN, BUTTON_N, EPD_BUSY, EPD_CS_N, EPD_DC, EPD_ENA, EPD_MISO, EPD_MOSI, EPD_RST_N, EPD_SCK, EPD_SRAM_CS_N, I2C_SCL, I2C_SDA, LOAD_OE_N, MCU_DONE, POWER_WARN_N, SCAN_MODE, SENSE_EN, SR_CLEAR_N, SR_CLOCK, SR_DATA, SR_LATCH, VCAP_ADC};
constexpr bool unique() {
    for (std::size_t i=0; i<sizeof(ASSIGNED)/sizeof(ASSIGNED[0]); ++i)
        for (std::size_t j=i+1; j<sizeof(ASSIGNED)/sizeof(ASSIGNED[0]); ++j)
            if (ASSIGNED[i]==ASSIGNED[j]) return false;
    return true;
}
static_assert(unique(), "Duplicate GPIO assignment");
static_assert(VCAP_ADC==1 && I2C_SDA==8 && I2C_SCL==9, "Fixed analog/I2C mapping changed");
} }
